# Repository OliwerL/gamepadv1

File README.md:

# gamepadv1
Simple ESP32-C3 Bluetooth LE gamepad with two analog joysticks and eight buttons (UP/DOWN/LEFT/RIGHT/A/B/X/Y), no R1/R2/L1/L2 triggers.

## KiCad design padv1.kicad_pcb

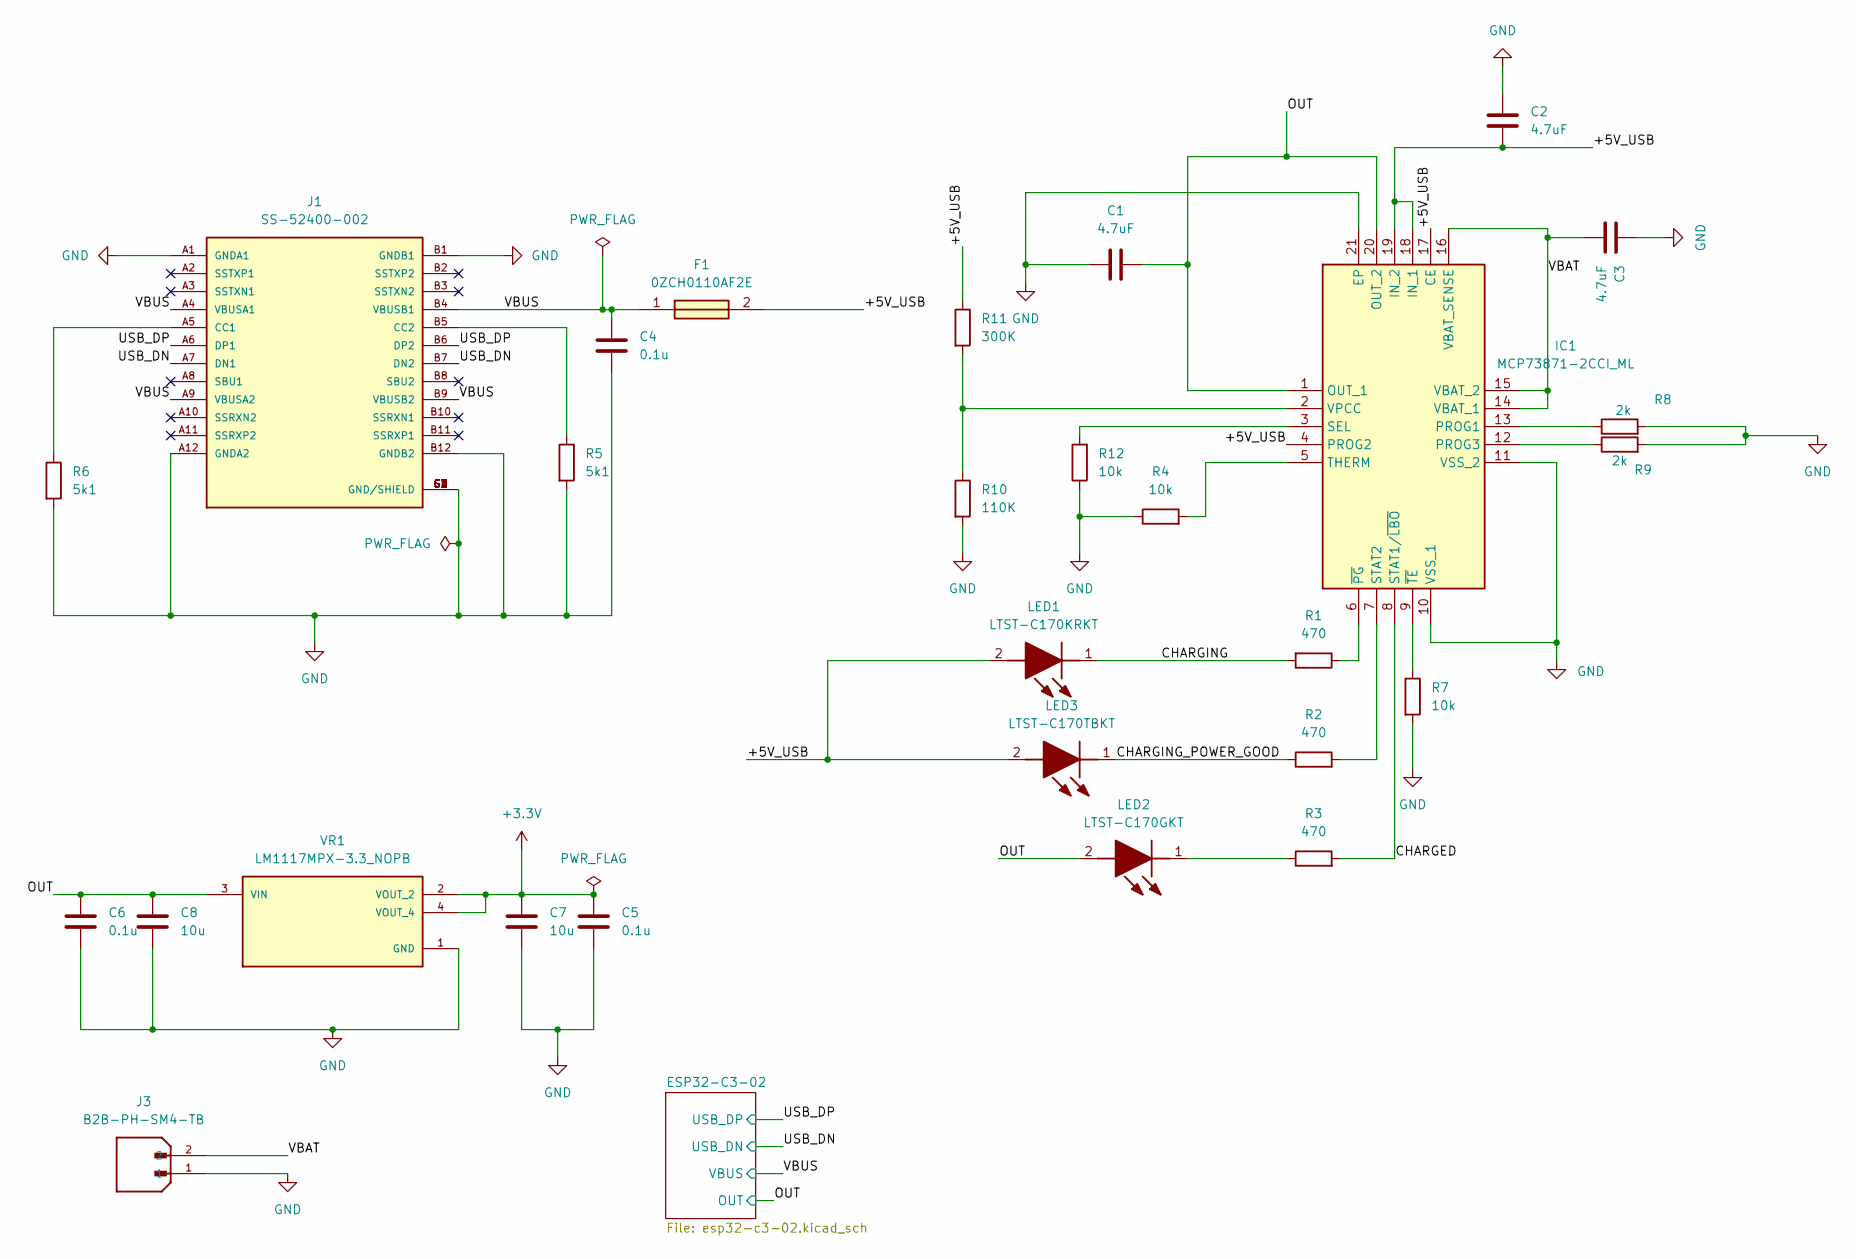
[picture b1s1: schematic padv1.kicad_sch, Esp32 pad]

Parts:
C1, C2, C3: 4.7uF; C_0805_2012Metric_Pad1.18x1.45mm_HandSolder
C4, C5, C6: 0.1u; C_0805_2012Metric_Pad1.18x1.45mm_HandSolder
C7, C8: 10u; C_0805_2012Metric_Pad1.18x1.45mm_HandSolder
F1: 0ZCH0110AF2E; FUSC3226X100N; Manufacturer_Part_Number 0ZCH0110AF2E
IC1: MCP73871-2CCI_ML; QFN50P400X400X100-21N-D; Manufacturer_Part_Number MCP73871-2CCI/ML; Mouser Part Number 579-MCP73871-2CCI/ML
J1: SS-52400-002; BELFUSE_SS-52400-002; PARTREV A0
J3: B2B-PH-SM4-TB; B2B-PH-SM4-TB_LF__SN_; PARTREV N/A
LED1: LTST-C170KRKT; LEDC2012X120N; Manufacturer_Part_Number LTST-C170KRKT; Mouser Part Number 859-LTST-C170KRKT
LED2: LTST-C170GKT; LEDC2012X120N; Manufacturer_Part_Number LTST-C170GKT; Mouser Part Number 859-LTST-C170GKT
LED3: LTST-C170TBKT; LEDC2012X120N; Manufacturer_Part_Number LTST-C170TBKT; Mouser Part Number 859-LTST-C170TBKT
R1, R2, R3: 470; R_0805_2012Metric_Pad1.20x1.40mm_HandSolder
R4, R7, R12: 10k; R_0805_2012Metric_Pad1.20x1.40mm_HandSolder
R5, R6: 5k1; R_0805_2012Metric_Pad1.20x1.40mm_HandSolder
R8, R9: 2k; R_0805_2012Metric_Pad1.20x1.40mm_HandSolder
R10: 110K; R_0805_2012Metric_Pad1.20x1.40mm_HandSolder
R11: 300K; R_0805_2012Metric_Pad1.20x1.40mm_HandSolder
VR1: LM1117MPX-3.3_NOPB; VREG_LM1117MPX-3.3_NOPB; PARTREV O

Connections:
+3.3V: C5.1, C7.1, VR1.2 (VOUT_2), VR1.4 (VOUT_4); also elsewhere on the board
/+5V_USB: C2.2, F1.2, IC1.4 (PROG2), IC1.17 (CE), IC1.18 (IN_1), IC1.19 (IN_2), LED1.2 (A), LED3.2 (A), R11.1
/CHARGED: IC1.8 (STAT1/~LBO), R3.2
/CHARGING: LED1.1 (K), R1.2
/CHARGING_POWER_GOOD: LED3.1 (K), R2.1
/OUT: C1.2, C6.1, C8.1, IC1.1 (OUT_1), IC1.20 (OUT_2), LED2.2 (A), VR1.3 (VIN); also elsewhere on the board
/USB_DN: J1.A7 (DN1), J1.B7 (DN2); also elsewhere on the board
/USB_DP: J1.A6 (DP1), J1.B6 (DP2); also elsewhere on the board
/VBAT: C3.2, IC1.14 (VBAT_1), IC1.15 (VBAT_2), IC1.16 (VBAT_SENSE), J3.2
/VBUS: C4.1, F1.1, J1.A4 (VBUSA1), J1.A9 (VBUSA2), J1.B4 (VBUSB1), J1.B9 (VBUSB2); also elsewhere on the board
GND: C1.1, C2.1, C3.1, C4.2, C5.2, C6.2, C7.2, C8.2, IC1.10 (VSS_1), IC1.11 (VSS_2), IC1.21 (EP), J1.A1 (GNDA1), J1.A12 (GNDA2), J1.B1 (GNDB1), J1.B12 (GNDB2), J1.G1 (GND/SHIELD), J1.G2 (GND/SHIELD), J1.G3 (GND/SHIELD), J1.G4 (GND/SHIELD), J1.S1 (GND/SHIELD), J1.S2 (GND/SHIELD), J1.S3 (GND/SHIELD), J1.S4 (GND/SHIELD), J3.1, R4.1, R5.2, R6.2, R7.2, R8.2, R9.2, R10.2, R12.1, VR1.1 (GND); also elsewhere on the board
unnamed: IC1.13 (PROG1), R8.1
unnamed: IC1.12 (PROG3), R9.1
unnamed: IC1.3 (SEL), R12.2
unnamed: IC1.7 (STAT2), R2.2
unnamed: IC1.5 (THERM), R4.2
unnamed: IC1.2 (VPCC), R10.1, R11.2
unnamed: IC1.6 (~PG), R1.1
unnamed: IC1.9 (~TE), R7.1
unnamed: J1.A5 (CC1), R6.1
unnamed: J1.B5 (CC2), R5.1
unnamed: LED2.1 (K), R3.1

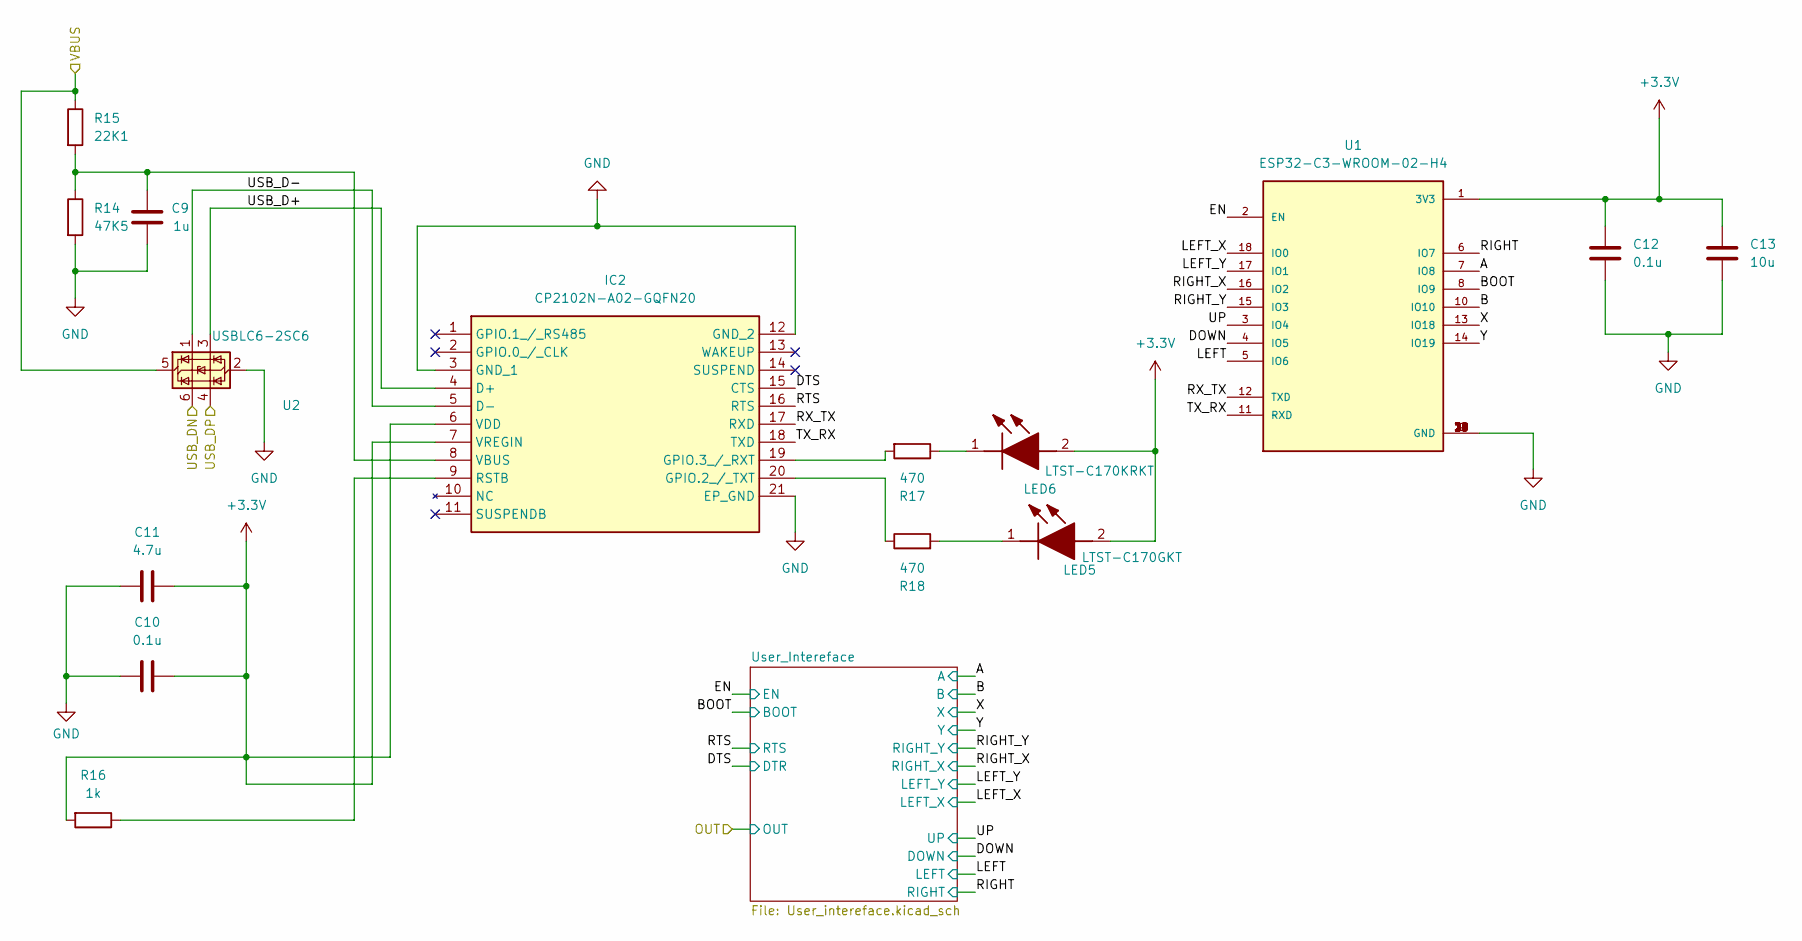
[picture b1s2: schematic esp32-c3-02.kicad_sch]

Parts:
C9: 1u; C_0805_2012Metric_Pad1.18x1.45mm_HandSolder
C10, C12: 0.1u; C_0805_2012Metric_Pad1.18x1.45mm_HandSolder
C11: 4.7u; C_0805_2012Metric_Pad1.18x1.45mm_HandSolder
C13: 10u; C_0805_2012Metric_Pad1.18x1.45mm_HandSolder
IC2: CP2102N-A02-GQFN20; CP2102NA02GQFN20; Mouser Part Number 634-CP2102NA02GQFN20
LED5: LTST-C170GKT; LEDC2012X120N; Manufacturer_Part_Number LTST-C170GKT; Mouser Part Number 859-LTST-C170GKT
LED6: LTST-C170KRKT; LEDC2012X120N; Manufacturer_Part_Number LTST-C170KRKT; Mouser Part Number 859-LTST-C170KRKT
R14: 47K5; R_0805_2012Metric_Pad1.20x1.40mm_HandSolder
R15: 22K1; R_0805_2012Metric_Pad1.20x1.40mm_HandSolder
R16: 1k; R_0805_2012Metric_Pad1.20x1.40mm_HandSolder
R17, R18: 470; R_0805_2012Metric_Pad1.20x1.40mm_HandSolder
U1: ESP32-C3-WROOM-02-H4; MODULE_ESP32-C3-WROOM-02-H4
U2: USBLC6-2SC6; SOT95P280X145-6N

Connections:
+3.3V: C10.2, C11.2, C12.1, C13.1, IC2.6 (VDD), IC2.7 (VREGIN), LED5.2 (A), LED6.2 (A), R16.2, U1.1 (3V3); also elsewhere on the board
/ESP32-C3-02/A: U1.7 (IO8); also elsewhere on the board
/ESP32-C3-02/B: U1.10 (IO10); also elsewhere on the board
/ESP32-C3-02/BOOT: U1.8 (IO9); also elsewhere on the board
/ESP32-C3-02/DOWN: U1.4 (IO5); also elsewhere on the board
/ESP32-C3-02/DTS: IC2.15 (CTS); also elsewhere on the board
/ESP32-C3-02/EN: U1.2 (EN); also elsewhere on the board
/ESP32-C3-02/LEFT: U1.5 (IO6); also elsewhere on the board
/ESP32-C3-02/LEFT_X: U1.18 (IO0); also elsewhere on the board
/ESP32-C3-02/LEFT_Y: U1.17 (IO1); also elsewhere on the board
/ESP32-C3-02/RIGHT: U1.6 (IO7); also elsewhere on the board
/ESP32-C3-02/RIGHT_X: U1.16 (IO2); also elsewhere on the board
/ESP32-C3-02/RIGHT_Y: U1.15 (IO3); also elsewhere on the board
/ESP32-C3-02/RTS: IC2.16 (RTS); also elsewhere on the board
/ESP32-C3-02/RX_TX: IC2.17 (RXD), U1.12 (TXD)
/ESP32-C3-02/TX_RX: IC2.18 (TXD), U1.11 (RXD)
/ESP32-C3-02/UP: U1.3 (IO4); also elsewhere on the board
/ESP32-C3-02/USB_D+: IC2.4 (D+), U2.3 (I/O2)
/ESP32-C3-02/USB_D-: IC2.5 (D-), U2.1 (I/O1)
/ESP32-C3-02/X: U1.13 (IO18); also elsewhere on the board
/ESP32-C3-02/Y: U1.14 (IO19); also elsewhere on the board
/USB_DN: U2.6 (I/O1); also elsewhere on the board
/USB_DP: U2.4 (I/O2); also elsewhere on the board
/VBUS: R15.1, U2.5 (VBUS); also elsewhere on the board
GND: C9.2, C10.1, C11.1, C12.2, C13.2, IC2.3 (GND_1), IC2.12 (GND_2), IC2.21 (EP_GND), R14.2, U1.9 (GND), U1.19 (GND), U1.20 (GND), U1.21 (GND), U1.22 (GND), U1.23 (GND), U1.24 (GND), U1.25 (GND), U1.26 (GND), U1.27 (GND), U1.28 (GND), U1.29 (GND), U1.30 (GND), U1.31 (GND), U1.32 (GND), U1.33 (GND), U1.34 (GND), U1.35 (GND), U1.36 (GND), U1.37 (GND), U1.38 (GND), U1.39 (GND), U2.2 (GND); also elsewhere on the board
unnamed: IC2.20 (GPIO.2_/_TXT), R18.1
unnamed: IC2.19 (GPIO.3_/_RXT), R17.2
unnamed: IC2.9 (RSTB), R16.1
unnamed: C9.1, IC2.8 (VBUS), R14.1, R15.2
unnamed: LED5.1 (K), R18.2
unnamed: LED6.1 (K), R17.1

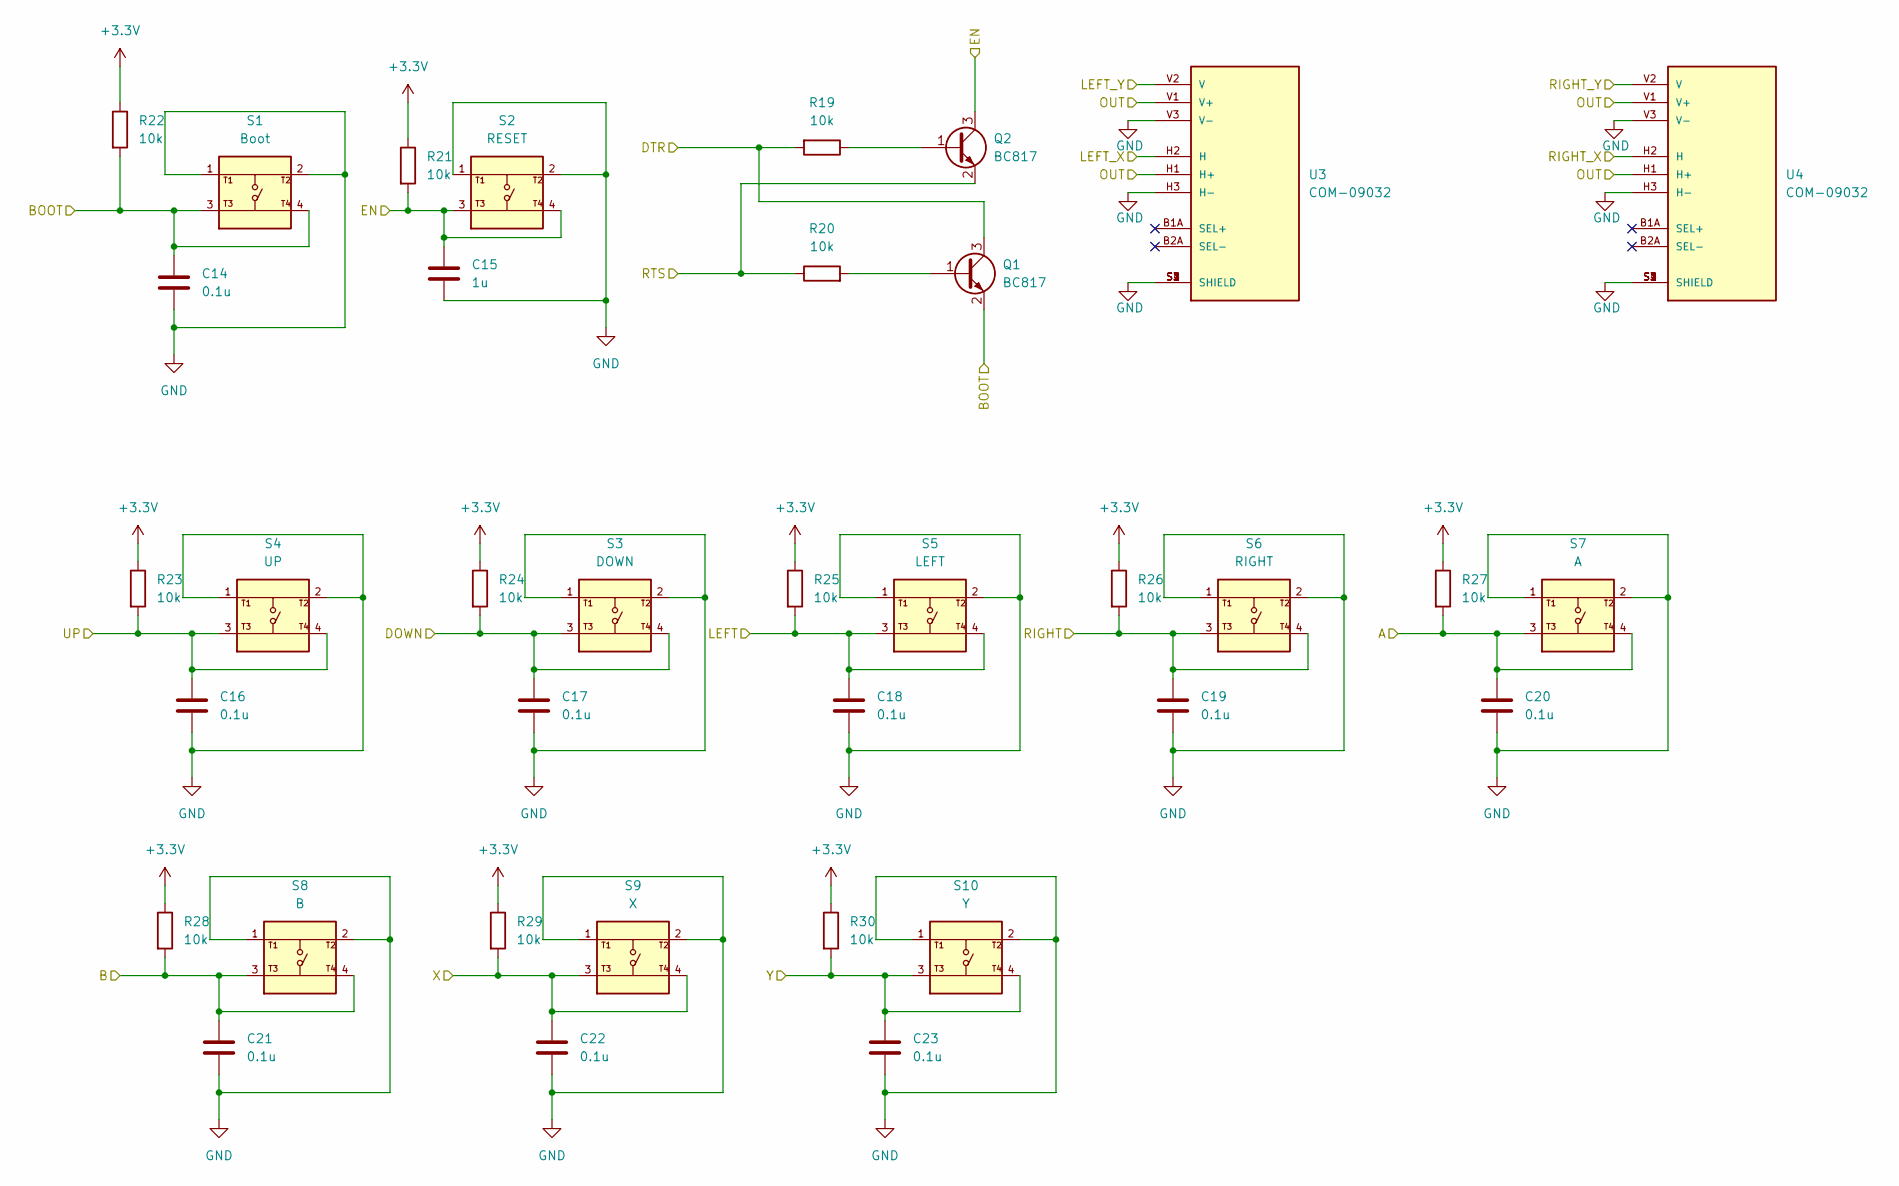
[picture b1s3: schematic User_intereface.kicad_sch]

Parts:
C14, C16, C17, C18, C19, C20, C21, C22, C23: 0.1u; C_0805_2012Metric_Pad1.18x1.45mm_HandSolder
C15: 1u; C_0805_2012Metric_Pad1.18x1.45mm_HandSolder
Q1, Q2: BC817; SOT95P230X110-3N
R19, R20, R21, R22, R23, R24, R25, R26, R27, R28, R29, R30: 10k; R_0805_2012Metric_Pad1.20x1.40mm_HandSolder
S1: Boot; SW_USLPT2819DT2TR; PARTREV P
S2: RESET; SW_USLPT2819DT2TR; PARTREV P
S3: DOWN; SW_USLPT2819DT2TR; PARTREV P
S4: UP; SW_USLPT2819DT2TR; PARTREV P
S5: LEFT; SW_USLPT2819DT2TR; PARTREV P
S6: RIGHT; SW_USLPT2819DT2TR; PARTREV P
S7: A; SW_USLPT2819DT2TR; PARTREV P
S8: B; SW_USLPT2819DT2TR; PARTREV P
S9: X; SW_USLPT2819DT2TR; PARTREV P
S10: Y; SW_USLPT2819DT2TR; PARTREV P
U3, U4: COM-09032; XDCR_COM-09032; PARTREV N/A

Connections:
+3.3V: R21.1, R22.1, R23.1, R24.1, R25.1, R26.1, R27.1, R28.1, R29.1, R30.1; also elsewhere on the board
/ESP32-C3-02/A: C20.1, R27.2, S7.3, S7.4; also elsewhere on the board
/ESP32-C3-02/B: C21.1, R28.2, S8.3, S8.4; also elsewhere on the board
/ESP32-C3-02/BOOT: C14.1, Q1.2 (E), R22.2, S1.3, S1.4; also elsewhere on the board
/ESP32-C3-02/DOWN: C17.1, R24.2, S3.3, S3.4; also elsewhere on the board
/ESP32-C3-02/DTS: Q1.3 (C), R19.2; also elsewhere on the board
/ESP32-C3-02/EN: C15.1, Q2.3 (C), R21.2, S2.3, S2.4; also elsewhere on the board
/ESP32-C3-02/LEFT: C18.1, R25.2, S5.3, S5.4; also elsewhere on the board
/ESP32-C3-02/LEFT_X: U3.H2 (H); also elsewhere on the board
/ESP32-C3-02/LEFT_Y: U3.V2 (V); also elsewhere on the board
/ESP32-C3-02/RIGHT: C19.1, R26.2, S6.3, S6.4; also elsewhere on the board
/ESP32-C3-02/RIGHT_X: U4.H2 (H); also elsewhere on the board
/ESP32-C3-02/RIGHT_Y: U4.V2 (V); also elsewhere on the board
/ESP32-C3-02/RTS: Q2.2 (E), R20.1; also elsewhere on the board
/ESP32-C3-02/UP: C16.1, R23.2, S4.3, S4.4; also elsewhere on the board
/ESP32-C3-02/X: C22.1, R29.2, S9.3, S9.4; also elsewhere on the board
/ESP32-C3-02/Y: C23.1, R30.2, S10.3, S10.4; also elsewhere on the board
/OUT: U3.H1 (H+), U3.V1 (V+), U4.H1 (H+), U4.V1 (V+); also elsewhere on the board
GND: C14.2, C15.2, C16.2, C17.2, C18.2, C19.2, C20.2, C21.2, C22.2, C23.2, S1.1, S1.2, S2.1, S2.2, S3.1, S3.2, S4.1, S4.2, S5.1, S5.2, S6.1, S6.2, S7.1, S7.2, S8.1, S8.2, S9.1, S9.2, S10.1, S10.2, U3.H3 (H-), U3.S1 (SHIELD), U3.S2 (SHIELD), U3.S3 (SHIELD), U3.S4 (SHIELD), U3.V3 (V-), U4.H3 (H-), U4.S1 (SHIELD), U4.S2 (SHIELD), U4.S3 (SHIELD), U4.S4 (SHIELD), U4.V3 (V-); also elsewhere on the board
unnamed: Q1.1 (B), R20.2
unnamed: Q2.1 (B), R19.1

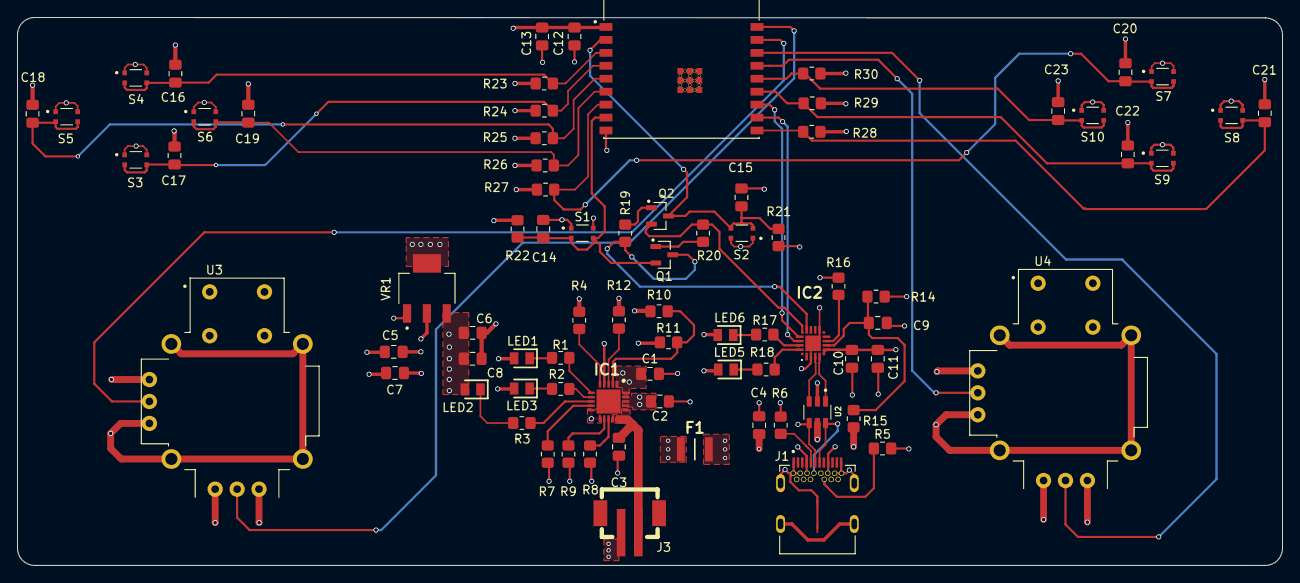
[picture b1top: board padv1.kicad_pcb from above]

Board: 4 copper layers, 146.6 x 63.5 mm, 79 parts (0 on the bottom side), 50 nets.

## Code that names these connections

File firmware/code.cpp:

#include <NimBLEDevice.h>

// ====== PINY (Twoje) ======
#define PIN_LEFT_X   0
#define PIN_LEFT_Y   1
#define PIN_RIGHT_X  2
#define PIN_RIGHT_Y  3
#define PIN_UP       4
#define PIN_DOWN     5
#define PIN_LEFT     6
#define PIN_RIGHT    7
#define PIN_A        8
#define PIN_B        10
#define PIN_X        18   // przenieś, jeśli użyjesz natywnego USB
#define PIN_Y        19

// ====== BLE NUS ======
#define NUS_SERVICE  "6E400001-B5A3-F393-E0A9-E50E24DCCA9E"
#define NUS_RX_CHAR  "6E400002-B5A3-F393-E0A9-E50E24DCCA9E" // PC -> ESP
#define NUS_TX_CHAR  "6E400003-B5A3-F393-E0A9-E50E24DCCA9E" // ESP -> PC

// ====== PARAMETRY OSI ======
#define SAMPLE_HZ      100           // częstotliwość wysyłania
#define DEADZONE_FRAC  0.06f         // ~6% martwej strefy
#define LPF_ALPHA      0.30f         // filtr wygładzający (0..1), 0=bez zmian
#define BOOT_CENTER_MS 800           // czas uśredniania środka przy starcie

// ====== ZMIENNE ======
NimBLECharacteristic* txChar;

struct AxisCal {
  int32_t center = 2048;   // środek
  int32_t minv   = 1600;   // obserwowane min
  int32_t maxv   = 2500;   // obserwowane max
  int32_t filt   = 0;      // stan przefiltrowany w skali -32768..32767
} cal[4]; // lx,ly,rx,ry

// czytanie przycisku (pullup): 1 = wciśnięty
static inline int btn(int pin){ return !digitalRead(pin); }

// szybkie mapowanie do int16 z deadzone i filtrem
int16_t map_axis(int raw, AxisCal &c) {
  // aktualizuj min/max „uczące się”
  if (raw < c.minv) c.minv = raw;
  if (raw > c.maxv) c.maxv = raw;
  int32_t span_pos = c.maxv - c.center;
  int32_t span_neg = c.center - c.minv;
  int32_t span = max(span_pos, span_neg);
  if (span < 200) span = 200; // minimalny sensowny zakres

  // przesunięcie względem środka
  float x = (float)(raw - c.center) / (float)span; // ~ -1..+1

  // martwa strefa
  float dz = DEADZONE_FRAC;
  if (x > -dz && x < dz) x = 0.f;
  else if (x >= dz) x = (x - dz) / (1.f - dz);
  else if (x <= -dz) x = (x + dz) / (1.f - dz);

  // skala do int16
  int32_t y = (int32_t)(x * 32767.f);
  // filtr IIR
  c.filt = (int32_t)((1.f - LPF_ALPHA) * c.filt + LPF_ALPHA * y);
  return (int16_t)c.filt;
}

// autokalibracja środka (przez ~BOOT_CENTER_MS na starcie)
void auto_center_boot() {
  uint32_t t0 = millis();
  uint32_t n = 0;
  uint64_t acc[4] = {0,0,0,0};
  while (millis() - t0 < BOOT_CENTER_MS) {
    acc[0] += analogRead(PIN_LEFT_X);
    acc[1] += analogRead(PIN_LEFT_Y);
    acc[2] += analogRead(PIN_RIGHT_X);
    acc[3] += analogRead(PIN_RIGHT_Y);
    n++;
    delay(2);
  }
  for (int i=0;i<4;i++) {
    int32_t c0 = (int32_t)(acc[i] / max<uint32_t>(n,1));
    cal[i].center = c0;
    cal[i].minv   = c0 - 300; // początkowy zapas
    cal[i].maxv   = c0 + 300;
    cal[i].filt   = 0;
  }
}

// „twardy” recal środka na aktualną pozycję (wywoływany z komendy BLE)
void recalibrate_now() {
  cal[0].center = analogRead(PIN_LEFT_X);
  cal[1].center = analogRead(PIN_LEFT_Y);
  cal[2].center = analogRead(PIN_RIGHT_X);
  cal[3].center = analogRead(PIN_RIGHT_Y);
  for (int i=0;i<4;i++) {
    cal[i].minv = cal[i].center - 300;
    cal[i].maxv = cal[i].center + 300;
    cal[i].filt = 0;
  }
}

// RX callback (opcjonalne komendy z PC: {"cmd":"cal"})
class RxCb : public NimBLECharacteristicCallbacks {
  void onWrite(NimBLECharacteristic* c) override {
    std::string s = c->getValue();
    if (s.find("\"cal\"") != std::string::npos) {
      recalibrate_now();
    }
  }
};

void setup() {
  // ADC na 3.3 V
  analogReadResolution(12);
  analogSetPinAttenuation(PIN_LEFT_X,  ADC_11db);
  analogSetPinAttenuation(PIN_LEFT_Y,  ADC_11db);
  analogSetPinAttenuation(PIN_RIGHT_X, ADC_11db);
  analogSetPinAttenuation(PIN_RIGHT_Y, ADC_11db);

  // przyciski
  pinMode(PIN_UP,    INPUT_PULLUP);
  pinMode(PIN_DOWN,  INPUT_PULLUP);
  pinMode(PIN_LEFT,  INPUT_PULLUP);
  pinMode(PIN_RIGHT, INPUT_PULLUP);
  pinMode(PIN_A,     INPUT_PULLUP);
  pinMode(PIN_B,     INPUT_PULLUP);
  pinMode(PIN_X,     INPUT_PULLUP);
  pinMode(PIN_Y,     INPUT_PULLUP);

  // autokalibracja środka przy starcie
  auto_center_boot();

  // BLE
  NimBLEDevice::init("ESP32C3_PAD");
  auto server  = NimBLEDevice::createServer();
  auto service = server->createService(NUS_SERVICE);
  txChar = service->createCharacteristic(NUS_TX_CHAR, NIMBLE_PROPERTY::READ | NIMBLE_PROPERTY::NOTIFY);
  auto rxChar = service->createCharacteristic(NUS_RX_CHAR, NIMBLE_PROPERTY::WRITE | NIMBLE_PROPERTY::WRITE_NR);
  rxChar->setCallbacks(new RxCb());
  service->start();

  auto adv = NimBLEDevice::getAdvertising();
  adv->addServiceUUID(NUS_SERVICE);
  adv->setScanResponse(true);
  NimBLEDevice::startAdvertising();
}

void loop() {
  // surowe
  int raw_lx = analogRead(PIN_LEFT_X);
  int raw_ly = analogRead(PIN_LEFT_Y);
  int raw_rx = analogRead(PIN_RIGHT_X);
  int raw_ry = analogRead(PIN_RIGHT_Y);

  // mapowanie -> int16
  int16_t lx = map_axis(raw_lx, cal[0]);
  int16_t ly = map_axis(raw_ly, cal[1]);
  int16_t rx = map_axis(raw_rx, cal[2]);
  int16_t ry = map_axis(raw_ry, cal[3]);

  // przyciski -> bitmask
  uint16_t k = 0;
  k |= btn(PIN_UP)    << 0;
  k |= btn(PIN_DOWN)  << 1;
  k |= btn(PIN_LEFT)  << 2;
  k |= btn(PIN_RIGHT) << 3;
  k |= btn(PIN_A)     << 4;
  k |= btn(PIN_B)     << 5;
  k |= btn(PIN_X)     << 6;
  k |= btn(PIN_Y)     << 7;

  // JSON (int16; wygodny do gier/emulatorów)
  char msg[120];
  int n = snprintf(msg, sizeof(msg),
                   "{\"lx\":%d,\"ly\":%d,\"rx\":%d,\"ry\":%d,\"k\":%u}",
                   (int)lx,(int)ly,(int)rx,(int)ry,k);

  txChar->setValue((uint8_t*)msg, n);
  txChar->notify();

  delay(1000 / SAMPLE_HZ);
}

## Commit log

2025-09-18 Initial project commit
2025-09-18 remove KiCad autosave and missing3Dmodels logs
2025-09-18 README
